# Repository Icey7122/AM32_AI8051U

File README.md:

# 80251 ESC Base on AI8051U

* [AM32](https://github.com/am32-firmware/AM32)<br>
* [ESC_Config_Tool](https://am32.ca/downloads)<br>
* [Bootloader](https://github.com/Icey7122/AM32_Bootloader_AI8051U)<br>

## Introduction
The AM32 firmware has been ported to the 80251 platform, and the controller has chosen as AI8051U. It can be compiled on Keil C251. At the same time, the bootloader program has been ported, and tool of Esc_Config_Tool_1_82_WIN can be used to configure and upgrade firmware for ESC.

## Hardware

### MCU
The resources of MCU([datasheet](https://www.stcaimcu.com/data/download/Datasheet/AI8051U.pdf)) are shown in the following figure,You can see that it has many peripheral resources.For more information, you can refer to the [STC](https://www.stcai.com/)<br>

### MCU Pins Diagram

Using PWMA to output 3 sets of complementary PWM for driving MOSFEET, Using PWMB for capturing external throttle signals, Using ADC to sample voltage and current, for low voltage protection and over current protection(But I'm not done yet). Using internal OPA and BEMF to estimate rotor position. TMR0 and TMR1 is used to calculate commutation time and motor timing.TMR2 is used for the serial port. TMR3 and TMR11 are used for the delay function (in fact, only one is needed). TMR4 is used to complete some periodic tasks.

### PINS

AH AL BH BL CH CL:  PWMA outputs;<br>
INPUT: PWMB used to capture external throttle signals;<br>
A_BEMF: A-Phase BEMF, connect to P46;<br>
B_BEMF: B-Phase BEMF, connect to P51;<br>
C_BEMF: C-Phase BEMF, connect to P50;<br>
CC_BEMF: Neutral point BEMF, connect to P45/P44(Note that for this mcu, P45 and P44 are the same pins);<br>
ADC_V: Voltage sampling channel;<br>
ADC_I: Current sampling channel;<br>
 
In order to unify the interrupt entry of OPA, the outputs of OPA are merged into P41, Using pin interrupts of P41 for zero crossing comparison processing.

P30 and P31 are used to download bootloader  via STC-LINK1, UART or internal USB.<br>

For detailed information, please refer to the schematic diagram.

## Config (New PCB)

### Flashing BootLoader
1. For empty chips, BootLoader needs to be flashed via STC-LINK1, UART or internal USB, Connect according to the diagram below.

2. Open the [Bootloader project](https://github.com/Icey7122/AM32_Bootloader_AI8051U) using AIapp-ISP and download it directly after compilation.

3. Use a one-wire serial port(You can connect the RX and TX of the USB to serial chip,such as CH340, together and then connect them to the board) to connect to ESC and use tools to configure and update firmware. I used CH340 to perfom, and the wiring is shown in the following figure.

    If the Bootloader is burned correctly, Open the configuration tool ***Esc_Config_Tool_1_82_WIN.exe*** and power on the ESC. Follow the steps in the following figure to click. When connecting for the first time, <font color=red>*'No EEprom'*</font> will be displayed!

    Directly click on ***Send Default Settings*** below to burn the default values. After successful burning, power on again. Connect again and click ***M1***. The default parameters we just burned will be displayed.

4. Flashing firmware and configurations<br>
    The firmware can be compiled using Keil C251, and the compiled firmware is in the ***\Objects*** folder.

    Open the HEX file with a text editor.I prefer to use VScode.To support HEX file editing, you need to install the ***Hex Editor or Intel HEX format*** plug-in. The plug-in can be installed in the extension market. After installation, open the HEX file.

    In this HEX file, please pay attention to the first line.<br>
    :03**0000**00023E58**65**<br>
    You should change the value of the **0000** to **1000** and the value of the **65** to **55**. Then save the file.<br>
    :03**1000**00023E58**55**<br>
    Note that the value of the **0000** is the starting address of the program, and the value of the **65** is the checksum. The value of the **1000** is the starting address of the program after the bootloader is burned. The value of the **55** is the new checksum. The starting address of the program after the bootloader is burned is 0x1000, so the value of the **0000** is changed to **1000**. The checksum is calculated by adding all the data in the line except the starting colon and the checksum itself, and then taking the two's complement of the last byte of the sum. The value of the **65** is changed to **55**. The specific calculation method can be found in the [link](https://en.wikipedia.org/wiki/Intel_HEX).
    If you use VScode with the plug-in, you can directly click on the **address value** to modify it, and the plug-in may automatically calculate the new checksum.

   Returning to the FLASH interface of the tool, we click on ***Load Firmware***, select the firmware we just modified, and the ***FLash Firmware*** button will pop up. Click to start updating the program. 

    After the update is completed, power on again and connect ESC again to configure ESC. The specific meaning of configuration values can be found in the following [links](https://github.com/AlkaMotors/AM32-MultiRotor-ESC-firmware/wiki/ESC-Settings-Explained).

## Hardware design
The circuit design is located in docs: [pcb](https://github.com/Icey7122/AM32_AI8051U/tree/main/docs), and the design is carried out using KiCAD, please note that the design is not particularly reasonable, please refer to it carefully.(Now I redesign the PCB on LCEDA, and the new PCB project also in docs folder.)

   New design:

## Test

The version I ported is V2.16, which supports signals such as dshot300, dshot600, and PWM.(But for some reason, I only implemented PWM, dshot can't be used).
* [Test Video(old PCB)](https://www.bilibili.com/video/BV1eZkvYuEUj)
* [Test Video(new PCB)](https://www.bilibili.com/video/BV1Huc3e8Egv)
## Reference
* [AM32](https://github.com/am32-firmware/AM32)
* [RISC-V AM32](https://github.com/TianpeiLee/AM32)

## Thanks
* HDU students have discovered some porting bugs, these bugs caused the ESC to be slow to respond.

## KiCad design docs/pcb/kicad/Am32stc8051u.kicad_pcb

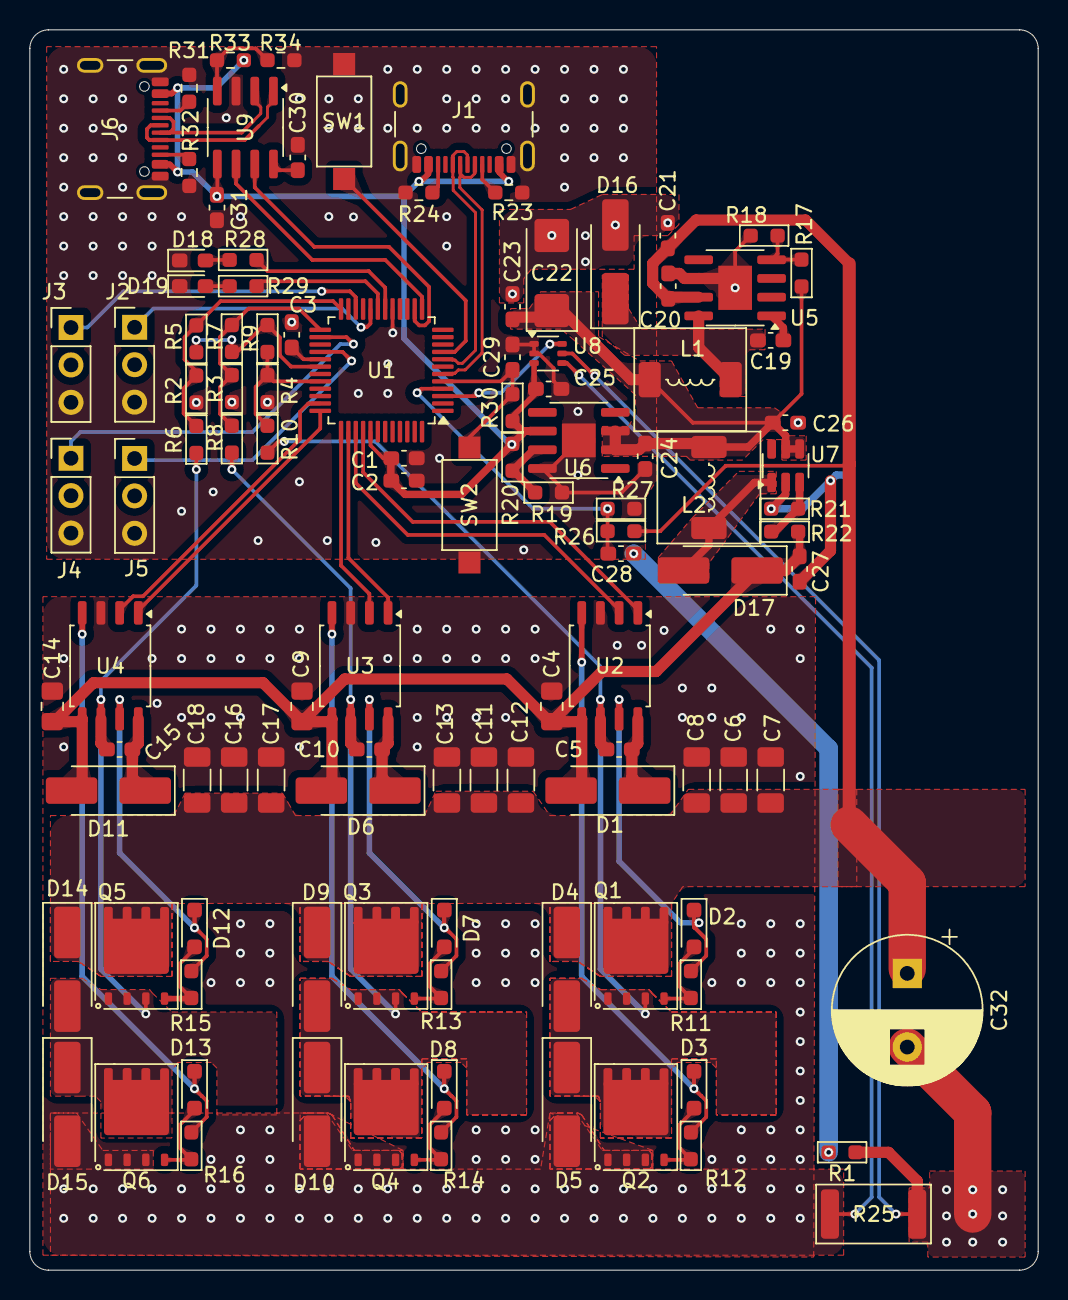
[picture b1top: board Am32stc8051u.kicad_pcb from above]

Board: 2 copper layers, 68.5 x 84.2 mm, 110 parts (0 on the bottom side), 66 nets.

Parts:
C1, C19, C20, C28, C29, C30, C31: 0.1uF; C_0603_1608Metric_Pad1.08x0.95mm_HandSolder
C2, C24, C26: 10uF; C_0603_1608Metric_Pad1.08x0.95mm_HandSolder
C3: 1uF; C_0603_1608Metric_Pad1.08x0.95mm_HandSolder
C4, C9, C14: C; C_0805_2012Metric_Pad1.18x1.45mm_HandSolder
C5, C10, C15: C; C_0603_1608Metric_Pad1.08x0.95mm_HandSolder
C6, C7, C8, C11, C12, C13, C16, C17, C18: C; C_1206_3216Metric_Pad1.33x1.80mm_HandSolder
C21, C27: 4.7uF; C_0603_1608Metric_Pad1.08x0.95mm_HandSolder
C22: 330uF; CP_EIA-6032-15_Kemet-U_Pad2.25x2.35mm_HandSolder
C23: 0.01uF; C_0603_1608Metric_Pad1.08x0.95mm_HandSolder
C25: 100nF; C_0603_1608Metric_Pad1.08x0.95mm_HandSolder
C32: C_Polarized; CP_Radial_D10.0mm_P5.00mm
D1, D4, D5, D6, D9, D10, D11, D14, D15, D16, D17: SS54; D_SMA_Handsoldering
D2, D3, D7, D8, D12, D13: 1N5819; D_SOD-323_HandSoldering
D18, D19: LED; LED_0603_1608Metric_Pad1.05x0.95mm_HandSolder
J1, J6: USB_C_Receptacle_USB2.0_16P; USB_C_Receptacle_GCT_USB4105-xx-A_16P_TopMnt_Horizontal
J2, J3, J4, J5: Conn_01x03_Pin; PinHeader_1x03_P2.54mm_Vertical
L1, L2: 10uH; L_6.3x6.3_H3
Q1, Q2, Q3, Q4, Q5, Q6: TPH1R005PL; Infineon_PG-TDSON-8
R1: 0R; R_0603_1608Metric_Pad0.98x0.95mm_HandSolder
R2, R3, R4, R27, R28, R29: 1K; R_0603_1608Metric_Pad0.98x0.95mm_HandSolder
R5, R6, R7, R8, R9, R10, R17, R20, R30, R33, R34: 10K; R_0603_1608Metric_Pad0.98x0.95mm_HandSolder
R11, R12, R13, R14, R15, R16: 10R; R_0603_1608Metric_Pad0.98x0.95mm_HandSolder
R18: 2.6K; R_0603_1608Metric_Pad0.98x0.95mm_HandSolder
R19: 1.11K; R_0603_1608Metric_Pad0.98x0.95mm_HandSolder
R21: 6.38K; R_0603_1608Metric_Pad0.98x0.95mm_HandSolder
R22: 100K; R_0603_1608Metric_Pad0.98x0.95mm_HandSolder
R23, R24, R26, R31, R32: 5.1K; R_0603_1608Metric_Pad0.98x0.95mm_HandSolder
R25: R_2512; R_2512_6332Metric
SW1, SW2: SW_Push; SW_SPST_CK_RS282G05A3
U1: STC8051U-32Kx; LQFP-48_7x7mm_P0.5mm
U2, U3, U4: EG2181; SOP-8_5.28x5.23mm_P1.27mm
U5: TPS5450; SOIC-8-1EP_3.9x4.9mm_P1.27mm_EP2.29x3mm
U6: RT9048; HSOP-8-1EP_3.9x4.9mm_P1.27mm_EP2.3x2.3mm
U7: MT3608; SOT-23-6
U8: INA199xxDCK; SOT-363_SC-70-6
U9: CH330N; SOIC-8_3.9x4.9mm_P1.27mm

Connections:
+5V: C1.1 (+), C2.1 (+), C25.1 (+), C31.2, J1.A4 (VBUS), J1.A9 (VBUS), J1.B4 (VBUS), J1.B9 (VBUS), J6.A4 (VBUS), J6.A9 (VBUS), J6.B4 (VBUS), J6.B9 (VBUS), R20.2 (-), R30.2 (-), R33.2, U1.41 (VCC), U6.6 (VOUT), U8.3 (V+), U9.5 (VCC)
+6V: C22.1, C23.2 (-), C24.1 (+), C26.2 (-), L1.2 (-), L2.1 (+), R17.1 (+), U6.2 (EN), U6.3 (VIN), U7.4 (EN), U7.5 (IN)
+10V: C4.1 (+), C9.1 (+), C14.1 (+), C27.2 (-), D1.2 (A), D6.2 (A), D11.2 (A), D17.1 (K), R22.1 (+), U2.5 (VCC), U3.5 (VCC), U4.5 (VCC)
/CH_D+: J6.A6 (D+), J6.B6 (D+), U9.1 (UD+)
/CH_D-: J6.A7 (D-), J6.B7 (D-), U9.2 (UD-)
/D+: J1.A6 (D+), J1.B6 (D+), U1.8 (D+)
/D-: J1.A7 (D-), J1.B7 (D-), U1.6 (D-)
/Half_Bridge_A/GND: C4.2 (-), C6.1 (+), C7.1 (+), C8.1 (+), C9.2 (-), C11.1 (+), C12.1 (+), C13.1 (+), C14.2 (-), C16.1 (+), C17.1 (+), C18.1 (+), D5.2 (A), D10.2 (A), D15.2 (A), Q2.1 (S), Q2.2 (S), Q2.3 (S), Q4.1 (S), Q4.2 (S), Q4.3 (S), Q6.1 (S), Q6.2 (S), Q6.3 (S), R25.1, U2.3 (GND), U3.3 (GND), U4.3 (GND), U8.4 (+)
/INPUT_1: J2.1, U1.20 (PWM5_3)
/INPUT_2: J3.1, U1.22 (PWM6_3)
/INPUT_3: J4.1, U1.26 (PWM7_3)
/INPUT_4: J5.1, U1.28 (PWM8_3)
/LED1: R29.1 (+), U1.19 (P20)
/LED2: R28.1 (+), U1.18 (P40)
/RxD2: U1.13 (RxD_2), U9.6 (TXD)
/TPS5450/VSENSE: R17.2 (-), R18.1 (+), U5.4 (VSENSE)
/TxD2: U1.14 (TxD_2), U9.7 (RXD)
ADC_Current: U1.3 (ADC6), U8.6
ADC_Voltage: C28.2 (-), R26.2 (-), R27.1 (+), U1.4 (ADC7)
A_H: U1.40 (PWM1P_2), U2.1 (HIN)
A_L: U1.39 (PWM1N_2), U2.2 (LIN)
A_OUT: C5.2 (-), D4.2 (A), D5.1 (K), Q1.1 (S), Q1.2 (S), Q1.3 (S), Q2.5 (D), R10.1 (+), U2.6 (VS)
BMF_A: R4.1 (+), R9.1 (+), R10.2 (-), U1.32 (CMP+)
BMF_B: R3.1 (+), R7.1 (+), R8.2 (-), U1.25 (CMP+_3)
BMF_C: R2.1 (+), R5.1 (+), R6.2 (-), U1.24 (CMP+_2)
B_H: U1.38 (PWM2P_2), U3.1 (HIN)
B_L: U1.37 (PWM2N_2), U3.2 (LIN)
B_OUT: C10.2 (-), D9.2 (A), D10.1 (K), Q3.1 (S), Q3.2 (S), Q3.3 (S), Q4.5 (D), R8.1 (+), U3.6 (VS)
C_H: U1.36 (PWM3P_2), U4.1 (HIN)
C_L: U1.35 (PWM3N_2), U4.2 (LIN)
C_OUT: C15.2 (-), D14.2 (A), D15.1 (K), Q5.1 (S), Q5.2 (S), Q5.3 (S), Q6.5 (D), R6.1 (+), U4.6 (VS)
EMF_COM: R5.2 (-), R7.2 (-), R9.2 (-), U1.30 (CMP-)
GND: C1.2 (-), C2.2 (-), C3.1 (+), C24.2 (-), C25.2 (-), C28.1 (+), C29.1 (+), C30.1, C31.1, D18.1 (K), D19.1 (K), J1.A1 (GND), J1.A12 (GND), J1.B1 (GND), J1.B12 (GND), J1.S1 (SHIELD), J2.3, J3.3, J4.3, J5.3, J6.A1 (GND), J6.A12 (GND), J6.B1 (GND), J6.B12 (GND), J6.S1 (SHIELD), R1.2 (-), R2.2 (-), R3.2 (-), R4.2 (-), R19.2 (-), R23.2, R24.2, R27.2 (-), R31.2, R32.2, R34.2, SW1.1, SW2.1, U1.17 (GND), U6.8 (GND), U6.9 (GND), U8.1 (REF), U8.2 (GND), U9.3 (GND)
GNDPWR: C20.1 (+), C21.1 (+), C22.2, C23.1 (+), C26.1 (+), C27.1 (+), C32.2, D16.2 (A), R1.1 (+), R18.2 (-), R21.1 (+), R25.2, U5.6 (GND), U5.9 (PowePAD), U7.2 (GND), U8.5 (-)
unnamed: C3.2 (-), U1.29 (UCAP)
unnamed: C5.1 (+), D1.1 (K), U2.8 (VB)
unnamed: C10.1 (+), D6.1 (K), U3.8 (VB)
unnamed: C15.1 (+), D11.1 (K), U4.8 (VB)
unnamed: C19.1 (+), U5.1 (BOOT)
unnamed: C19.2 (-), D16.1 (K), L1.1 (+), U5.8 (PH)
unnamed: C29.2 (-), R30.1 (+), SW2.2, U1.5 (RST)
unnamed: D2.2 (A), Q1.4 (G), R11.1 (+)
unnamed: D2.1 (K), R11.2 (-), U2.7 (HO)
unnamed: D3.2 (A), Q2.4 (G), R12.1 (+)
unnamed: D3.1 (K), R12.2 (-), U2.4 (LO)
unnamed: D7.2 (A), Q3.4 (G), R13.1 (+)
unnamed: D7.1 (K), R13.2 (-), U3.7 (HO)
unnamed: D8.2 (A), Q4.4 (G), R14.1 (+)
unnamed: D8.1 (K), R14.2 (-), U3.4 (LO)
unnamed: D12.2 (A), Q5.4 (G), R15.1 (+)
unnamed: D12.1 (K), R15.2 (-), U4.7 (HO)
unnamed: D13.2 (A), Q6.4 (G), R16.1 (+)
unnamed: D13.1 (K), R16.2 (-), U4.4 (LO)
unnamed: D17.2 (A), L2.2 (-), U7.1 (SW)
unnamed: D18.2 (A), R28.2 (-)
unnamed: D19.2 (A), R29.2 (-)
unnamed: J1.A5 (CC1), R23.1
unnamed: J1.B5 (CC2), R24.1
unnamed: J6.A5 (CC1), R31.1
unnamed: J6.B5 (CC2), R32.1
unnamed: R19.1 (+), R20.1 (+), U6.7 (ADJ)
unnamed: R21.2 (-), R22.2 (-), U7.3 (FB)
unnamed: SW1.2, U1.9 (P32)
unnamed: C30.2, U9.8 (V3)
unnamed: R33.1, R34.1, U9.4 (~RTS)
VBAT: C6.2 (-), C7.2 (-), C8.2 (-), C11.2 (-), C12.2 (-), C13.2 (-), C16.2 (-), C17.2 (-), C18.2 (-), C20.2 (-), C21.2 (-), C32.1, D4.1 (K), D9.1 (K), D14.1 (K), Q1.5 (D), Q3.5 (D), Q5.5 (D), R26.1 (+), U5.7 (VIN)

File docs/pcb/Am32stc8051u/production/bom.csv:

Designator,Footprint,Quantity,Value,LCSC Part #
"C1, C19, C20, C28, C29, C30, C31",0603,7,0.1uF,
"C10, C15, C5",0603,3,C,
"C11, C12, C13, C16, C17, C18, C6, C7, C8",1206,9,C,
"C14, C4, C9",0805,3,C,
"C2, C24, C26",0603,3,10uF,
"C21, C27",0603,2,4.7uF,
C22,CP_EIA-6032-15_Kemet-U_Pad2.25x2.35mm_HandSolder,1,330uF,
C23,0603,1,0.01uF,
C25,0603,1,100nF,
C3,0603,1,1uF,
C32,CP_Radial_D10.0mm_P5.00mm,1,C_Polarized,
"D1, D10, D11, D14, D15, D16, D17, D4, D5, D6, D9",D_SMA_Handsoldering,11,SS54,
"D12, D13, D2, D3, D7, D8",D_SOD-323_HandSoldering,6,1N5819,
"D18, D19",0603,2,LED,
"J1, J6",USB_C_Receptacle_GCT_USB4105-xx-A_16P_TopMnt_Horizontal,2,USB_C_Receptacle_USB2.0_16P,
"J2, J3, J4, J5",PinHeader_1x03_P2.54mm_Vertical,4,Conn_01x03_Pin,
"L1, L2",L_6.3x6.3_H3,2,10uH,
"Q1, Q2, Q3, Q4, Q5, Q6",Infineon_PG-TDSON-8,6,TPH1R005PL,
R1,0603,1,0R,
"R10, R17, R20, R30, R33, R34, R5, R6, R7, R8, R9",0603,11,10K,
"R11, R12, R13, R14, R15, R16",0603,6,10R,
R18,0603,1,2.6K,
R19,0603,1,1.11K,
"R2, R27, R28, R29, R3, R4",0603,6,1K,
R21,0603,1,6.38K,
R22,0603,1,100K,
"R23, R24, R26, R31, R32",0603,5,5.1K,
R25,2512,1,R_2512,
"SW1, SW2",SW_SPST_CK_RS282G05A3,2,SW_Push,
U1,LQFP-48_7x7mm_P0.5mm,1,STC8051U-32Kx,
"U2, U3, U4",SOP-8_5.28x5.23mm_P1.27mm,3,EG2181,
U5,SOIC-8-1EP_3.9x4.9mm_P1.27mm_EP2.29x3mm,1,TPS5450,
U6,HSOP-8-1EP_3.9x4.9mm_P1.27mm_EP2.3x2.3mm,1,RT9048,
U7,SOT-23-6,1,MT3608,
U8,SOT-363_SC-70-6,1,INA199xxDCK,
U9,SOIC-8_3.9x4.9mm_P1.27mm,1,CH330N,

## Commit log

2024-12-22 Add project
2024-12-22 deleted: AM32_AI8051U.uvgui.17263
2024-12-22 modified: README.md
2024-12-22 modify readme
2024-12-22 Add hardware design
2025-01-12 add hardware group
2025-01-13 add lceda
2025-01-13 add details
2025-01-19 add voltage limit , current limit and serial_telemetry.
2025-01-19 Update README.md
    Now, current limit, voltage sampling and serial telemetry can be used
2025-01-20 add .gitignore
2025-01-20 modified: .gitignore
2025-01-20 add .gitignore and change some thing
2025-01-20 fix change data type
2025-01-24 change head files
2025-01-31 change something
2025-02-01 change pcb address
2025-03-06 support vofa+
2025-03-06 change some setting
2025-03-08 fix some bugs
2025-08-22 fix some bugs and update to 2.18
2025-08-22 Update README.md
    add thanks
